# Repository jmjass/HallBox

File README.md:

# HallBox
 Hall effect box using void switches

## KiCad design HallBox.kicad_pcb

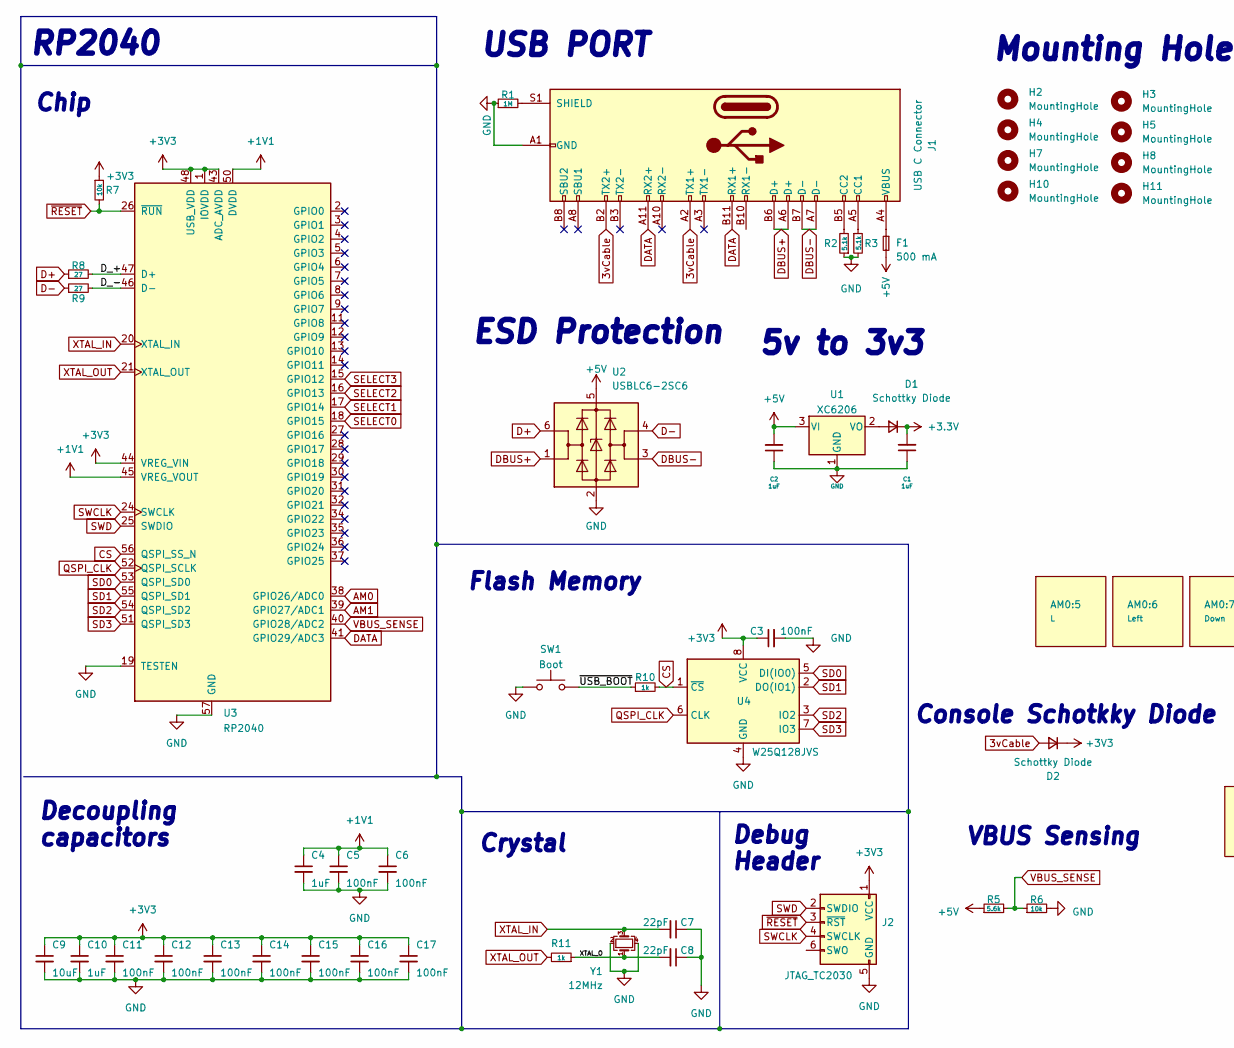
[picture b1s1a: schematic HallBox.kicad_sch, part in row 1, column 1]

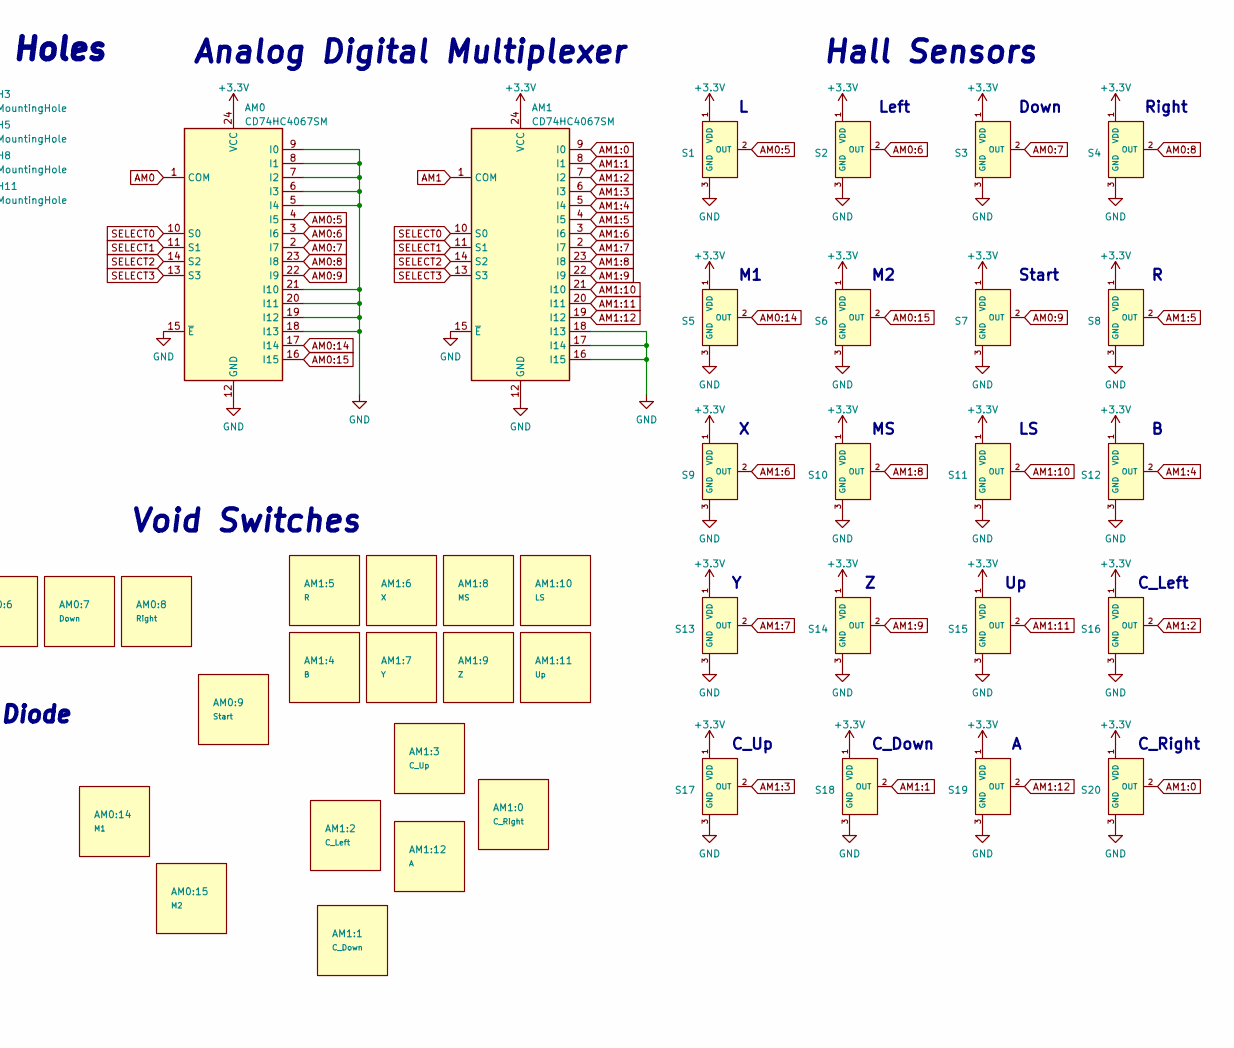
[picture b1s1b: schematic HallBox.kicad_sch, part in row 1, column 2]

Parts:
AM0, AM1: CD74HC4067SM; SSOP-24_5.3x8.2mm_P0.65mm
AM0:5: L; VoidSwitch_1u_SMD
AM0:6: Left; VoidSwitch_1u_SMD
AM0:7: Down; VoidSwitch_1u_SMD
AM0:8: Right; VoidSwitch_1u_SMD
AM0:9: Start; VoidSwitch_1u_SMD
AM0:14: M1; VoidSwitch_1u_SMD
AM0:15: M2; VoidSwitch_1u_SMD
AM1:0: C_Right; VoidSwitch_1u_SMD
AM1:1: C_Down; VoidSwitch_1u_SMD
AM1:2: C_Left; VoidSwitch_1u_SMD
AM1:3: C_Up; VoidSwitch_1u_SMD
AM1:4: B; VoidSwitch_1u_SMD
AM1:5: R; VoidSwitch_1u_SMD
AM1:6: X; VoidSwitch_1u_SMD
AM1:7: Y; VoidSwitch_1u_SMD
AM1:8: MS; VoidSwitch_1u_SMD
AM1:9: Z; VoidSwitch_1u_SMD
AM1:10: LS; VoidSwitch_1u_SMD
AM1:11: Up; VoidSwitch_1u_SMD
AM1:12: A; VoidSwitch_1u_SMD
C1, C2, C4, C10: 1uF; C_0402_1005Metric; LCSC C52923
C3, C5, C6, C11, C12, C13, C14, C15, C16, C17: 100nF; C_0402_1005Metric; LCSC C1525
C7, C8: 22pF; C_0402_1005Metric; LCSC C1555
C9: 10uF; C_0402_1005Metric; LCSC C15525
D1, D2: Schottky Diode; CUSTOM D_SOD-123; LCSC C130880
F1: 500 mA; Fuse_1206_3216Metric
H2, H3, H4, H5, H7, H8, H10, H11: MountingHole; MountingHole_2.2mm_M2_ISO14580_Pad
J1: USB C Connector; TYPE-C_24P_QCHT; LCSC C456013
J2: JTAG_TC2030; CON_TC2030_outlined
R1: 1M; R_0603_1608Metric; LCSC C25190
R2, R3: 5.1k; R_0402_1005Metric; LCSC C25744
R5: 5.6k; R_0603_1608Metric
R6: 10k; R_0603_1608Metric
R7: 10k; R_0402_1005Metric; LCSC C25744
R8, R9: 27; R_0603_1608Metric; LCSC C25190
R10, R11: 1k; R_0402_1005Metric; LCSC C11702
S1, S2, S3, S4, S5, S6, S7, S8, S9, S10, S11, S12, S13, S14, S15, S16, S17, S18, S19, S20: Hall_Sensor; SOT-23; MPN GH39FKSW; LCSC Part C266230
SW1: Boot; SW_SPST_SKQG_WithStem; LCSC C5156480
U1: XC6206; SOT-23; LCSC C5446
U2: USBLC6-2SC6; SOT-23-6
U3: RP2040; RP2040-QFN-56; LCSC C2040
U4: W25Q128JVS; SOIC-8_5.23x5.23mm_P1.27mm; LCSC C97521
Y1: 12MHz; Crystal_SMD_3225-4Pin_3.2x2.5mm; LCSC C9002

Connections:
3vCable: D2.2 (A), J1.A2 (TX1+), J1.B2 (TX2+)
+1V1: C4.1, C5.1, C6.1, U3.23 (DVDD), U3.45 (VREG_VOUT), U3.50 (DVDD)
+5V: C2.2, F1.2, R5.1, U1.3 (VI), U2.5 (VBUS)
/D_+: R8.2, U3.47 (D+)
/D_-: R9.2, U3.46 (D-)
/XTAL_O: C8.2, R11.1, Y1.1
/~USB_BOOT: R10.1, SW1.2
AM0: AM0.1 (COM), U3.38 (GPIO26/ADC0)
AM0:5: AM0.4 (I5), S1.2 (OUT)
AM0:6: AM0.3 (I6), S2.2 (OUT)
AM0:7: AM0.2 (I7), S3.2 (OUT)
AM0:8: AM0.23 (I8), S4.2 (OUT)
AM0:9: AM0.22 (I9), S7.2 (OUT)
AM0:14: AM0.17 (I14), S5.2 (OUT)
AM0:15: AM0.16 (I15), S6.2 (OUT)
AM1: AM1.1 (COM), U3.39 (GPIO27/ADC1)
AM1:0: AM1.9 (I0), S20.2 (OUT)
AM1:1: AM1.8 (I1), S18.2 (OUT)
AM1:2: AM1.7 (I2), S16.2 (OUT)
AM1:3: AM1.6 (I3), S17.2 (OUT)
AM1:4: AM1.5 (I4), S12.2 (OUT)
AM1:5: AM1.4 (I5), S8.2 (OUT)
AM1:6: AM1.3 (I6), S9.2 (OUT)
AM1:7: AM1.2 (I7), S13.2 (OUT)
AM1:8: AM1.23 (I8), S10.2 (OUT)
AM1:9: AM1.22 (I9), S14.2 (OUT)
AM1:10: AM1.21 (I10), S11.2 (OUT)
AM1:11: AM1.20 (I11), S15.2 (OUT)
AM1:12: AM1.19 (I12), S19.2 (OUT)
CS: R10.2, U3.56 (QSPI_SS_N), U4.1 (~CS)
D+: R8.1, U2.6 (I/O1)
D-: R9.1, U2.4 (I/O2)
DATA: J1.A11 (RX2+), J1.B11 (RX1+), U3.41 (GPIO29/ADC3)
DBUS+: J1.A6 (D+), J1.B6 (D+), U2.1 (I/O1)
DBUS-: J1.A7 (D-), J1.B7 (D-), U2.3 (I/O2)
GND: AM0.5 (I4), AM0.6 (I3), AM0.7 (I2), AM0.8 (I1), AM0.9 (I0), AM0.12 (GND), AM0.15 (~E), AM0.18 (I13), AM0.19 (I12), AM0.20 (I11), AM0.21 (I10), AM1.12 (GND), AM1.15 (~E), AM1.16 (I15), AM1.17 (I14), AM1.18 (I13), C1.1, C2.1, C3.2, C4.2, C5.2, C6.2, C7.1, C8.1, C9.2, C10.2, C11.2, C12.2, C13.2, C14.2, C15.2, C16.2, C17.2, J1.A1 (GND), J1.A12 (GND), J1.B1 (GND), J1.B12 (GND), J2.5 (GND), R1.1, R2.1, R3.2, R6.2, S1.3 (GND), S2.3 (GND), S3.3 (GND), S4.3 (GND), S5.3 (GND), S6.3 (GND), S7.3 (GND), S8.3 (GND), S9.3 (GND), S10.3 (GND), S11.3 (GND), S12.3 (GND), S13.3 (GND), S14.3 (GND), S15.3 (GND), S16.3 (GND), S17.3 (GND), S18.3 (GND), S19.3 (GND), S20.3 (GND), SW1.1, U1.1 (GND), U2.2 (GND), U3.19 (TESTEN), U3.57 (GND), U4.4 (GND), Y1.2, Y1.4
unnamed: D1.2 (A), U1.2 (VO)
unnamed: F1.1, J1.A4 (VBUS), J1.A9 (VBUS), J1.B4 (VBUS), J1.B9 (VBUS)
unnamed: J1.A5 (CC1), R3.1
unnamed: J1.B5 (CC2), R2.2
unnamed: J1.S1 (SHIELD), R1.2
QSPI_CLK: U3.52 (QSPI_SCLK), U4.6 (CLK)
SD0: U3.53 (QSPI_SD0), U4.5 (DI(IO0))
SD1: U3.55 (QSPI_SD1), U4.2 (DO(IO1))
SD2: U3.54 (QSPI_SD2), U4.3 (IO2)
SD3: U3.51 (QSPI_SD3), U4.7 (IO3)
SELECT0: AM0.10 (S0), AM1.10 (S0), U3.18 (GPIO15)
SELECT1: AM0.11 (S1), AM1.11 (S1), U3.17 (GPIO14)
SELECT2: AM0.14 (S2), AM1.14 (S2), U3.16 (GPIO13)
SELECT3: AM0.13 (S3), AM1.13 (S3), U3.15 (GPIO12)
SWCLK: J2.4 (SWCLK), U3.24 (SWCLK)
SWD: J2.2 (SWDIO), U3.25 (SWDIO)
VBUS_SENSE: R5.2, R6.1, U3.40 (GPIO28/ADC2)
XTAL_IN: C7.2, U3.20 (XTAL_IN), Y1.3
XTAL_OUT: R11.2, U3.21 (XTAL_OUT)
~RESET: J2.3 (~RST), R7.2, U3.26 (~RUN)

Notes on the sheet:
VBUS Sensing
Analog Digital Multiplexer
C_Left
C_Right
Hall Sensors
Left
C_Down
Chip
Flash Memory
Right
Void Switches
C_Up
USB PORT
5v to 3v3
Decoupling capacitors
Mounting Holes
RP2040
Console Schotkky Diode
Down
Start
Debug Header
Crystal
ESD Protection

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
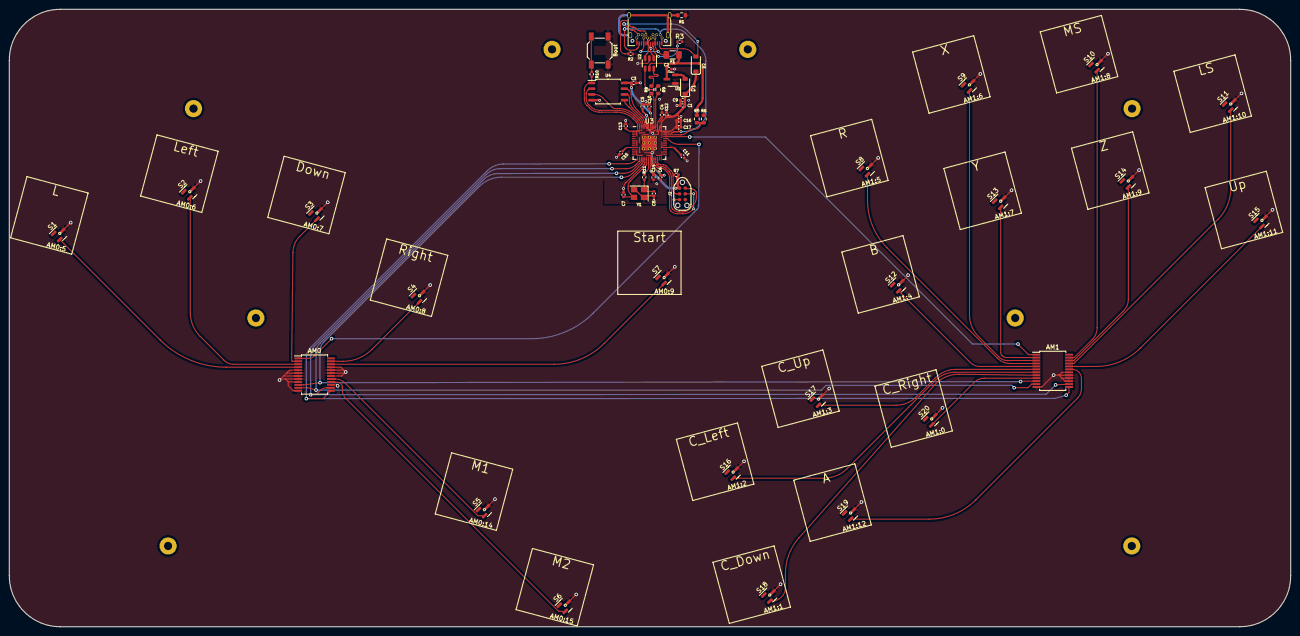
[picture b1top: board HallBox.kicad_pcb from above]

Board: 2 copper layers, 282.7 x 136.2 mm, 88 parts (0 on the bottom side), 57 nets.

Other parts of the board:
H1, H6: MountingHole; MountingHole_2.2mm_M2_ISO14580_Pad

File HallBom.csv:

Comment,Designator,Footprint,LCSC
1uF,"C1,C2,C4,C10",Capacitor_SMD:C_0402_1005Metric,C52923
100nF,"C3,C5,C6,C11,C12,C13,C14,C15,C16,C17",Capacitor_SMD:C_0402_1005Metric,C1525
10uF,C9,Capacitor_SMD:C_0402_1005Metric,C15525
22pF,"C7,C8",Capacitor_SMD:C_0402_1005Metric,C1555
Schottky Diode,"D1,D2",qw-footprints:CUSTOM D_SOD-123,C130880
Fuse_Small,F1,Fuse:Fuse_1206_3216Metric,C70069
USB C Connector,J1,qw-footprints:TYPE-C_24P_QCHT,C456013
1M,R1,Resistor_SMD:R_0603_1608Metric,C22935
5.1k,"R2,R3",Resistor_SMD:R_0402_1005Metric,C26000
470,R4,Resistor_SMD:R_0402_1005Metric,C25167
5.6k,R5,Resistor_SMD:R_0603_1608Metric,C23189
27,"R8,R9",Resistor_SMD:R_0603_1608Metric,C25190
1k,"R10,R11",Resistor_SMD:R_0402_1005Metric,C11702
Boot,SW1,Button_Switch_SMD:SW_SPST_SKQG_WithStem,C202424
XC6206,U1,Package_TO_SOT_SMD:SOT-23,C5446
USBLC6-2SC6,U2,Package_TO_SOT_SMD:SOT-23-6,C5261088
RP2040,U3,qw-footprints:RP2040-QFN-56,C2040
W25Q128JVS,U4,Package_SO:SOIC-8_5.23x5.23mm_P1.27mm,C97521
12MHz,Y1,Crystal:Crystal_SMD_3225-4Pin_3.2x2.5mm,C9002
Hall Sensor,"S1,S2,S3,S4,S5,S6,S7,S8,S9,S10,S11,S12,S13,S14,S15,S16,S17,S18,S19,S20",Package_TO_SOT_SMD:SOT-23,GH39FKSW
Analog Digital Multiplexer,"AM0,AM1",Package_SO:SSOP-24_5.3x8.2mm_P0.65mm,C98457

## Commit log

2023-04-12 updated pcb
